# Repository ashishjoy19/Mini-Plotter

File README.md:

# Electronics 

# ⚡ Mini Plotter V2 – Electronics Documentation

## Overview

This document covers **the electronics subsystem** of the Mini Plotter V project.

It is intended as a **reference for coworkers, fabrication, debugging, and replication** of the electronics and PCB.

---

## Scope

### Included
- PCB design reference
- Power architecture
- Microcontroller pin mapping
- Stepper driver connections
- Peripheral interfaces

**Board Details**

| Parameter | Value |
|--------|------|
| PCB Name | Mini Plotter V2 – Electronics |
| Layers | 2 |
| Thickness | 1.6 mm |
| Copper Weight | 1 oz |
| Assembly | Through-hole + SMD |
| Logic Voltage | 3.3V |
| Motor Voltage | 5V DC |

## Power Architecture

### Power Input
- External DC input - USB C (Power only)
- Recommended supply: **5V**

### Voltage Rails
- **Motor Rail:** Direct from input to stepper drivers
- **Logic Rail:** Regulated 3.3V for MCU and peripherals

### Electrical Notes

⚠️ **Important**
- Power supply must handle motor current peaks
- Logic and motor grounds are common
- Do not connect or disconnect motors while powered

---

## MCU Pin Mapping

## GPIO Pin Mapping (Grouped)

### Motor 1 (Stepper)
| Label | GPIO |
|-----|------|
| IN1 | GPIO 23 |
| IN2 | GPIO 22 |
| IN3 | GPIO 21 |
| IN4 | GPIO 19 |

### Motor 2 (Stepper)
| Label | GPIO |
|-----|------|
| IN5 | GPIO 18 |
| IN6 | GPIO 17 |
| IN7 | GPIO 16 |
| IN8 | GPIO 4 |

### Servo Motor
| Label | GPIO |
|------|------|
| SIGNAL | GPIO 13 |
| VCC | 5V |
| GND | GND |

### Limit Switches
| Switch | Signal GPIO | Ground |
|-------|------------|--------|
| X Limit | GPIO 27 | GND |
| Y Limit | GPIO 14 | GND |

---

# ⚡ ESP32-WROOM-32E – PCB Design & Boot Guidelines

This document provides **electronics design guidelines** for using the **ESP32-WROOM-32E** module in custom PCBs.

It focuses on:
- Boot and flashing requirements
- Strapping pins and default states
- Pins to avoid or use with caution
- Minimum required external circuitry
- PCB layout considerations

---

## ESP32-WROOM-32E Overview

- MCU: ESP32 (dual-core Xtensa LX6)
- Operating Voltage: **3.3V**
- Wi-Fi + Bluetooth on-module
- Integrated antenna (keep-out required)

⚠️ **All GPIOs are 3.3V only. Do NOT apply 5V.**

---

## Minimum Circuit for Boot & Flash

::contentReference[oaicite:0]{index=0}

### Mandatory Connections

| Pin | Requirement |
|----|------------|
| 3V3 | Stable 3.3V supply (≥ 600 mA peak) |
| GND | Solid ground connection |
| EN | Pulled HIGH (via 10kΩ) |
| IO0 | Pulled HIGH (via 10kΩ) |
| TX0 (GPIO1) | UART TX for flashing |
| RX0 (GPIO3) | UART RX for flashing |

---

## Boot & Flash Logic

### Boot Mode Selection

| IO0 State | Boot Mode |
|---------|-----------|
| HIGH | Normal boot (flash) |
| LOW | UART download (flashing) |

To flash firmware:
- **IO0 = LOW**
- **EN toggled LOW → HIGH (reset)**

---

## Strapping Pins (CRITICAL)

These pins are sampled **at reset**.  
Incorrect levels will prevent booting.

| GPIO | Default State | Function |
|----|--------------|---------|
| GPIO0 | Pull-up | Boot mode select |
| GPIO2 | Pull-down | Must be LOW at boot |
| GPIO4 | Pull-down | Boot config |
| GPIO5 | Pull-up | Boot config |
| GPIO12 | Pull-down | Flash voltage select |
| GPIO15 | Pull-up | Boot config |

⚠️ **Do not drive these pins externally at boot unless you know the impact.**

---

## Pin Usage Guidelines

### Pins to Avoid (or Use Carefully)

| GPIO | Reason |
|----|-------|
| GPIO6–11 | Connected to internal flash (DO NOT USE) |
| GPIO0 | Boot mode pin |
| GPIO2 | Must be LOW during boot |
| GPIO12 | Affects flash voltage |
| GPIO15 | Boot strapping pin |

---

### Recommended Safe GPIOs

| GPIO | Notes |
|----|------|
| GPIO4 | Safe after boot |
| GPIO5 | Safe after boot |
| GPIO16–19 | General purpose |
| GPIO21–23 | I²C / SPI friendly |
| GPIO25–27 | ADC capable |
| GPIO32–33 | ADC + low power |
| GPIO34–39 | Input-only (ADC) |

---

## Pull-Up / Pull-Down Requirements

### Required External Resistors

| Pin | Recommended |
|----|-------------|
| EN | 10kΩ pull-up to 3.3V |
| IO0 | 10kΩ pull-up |
| GPIO2 | 10kΩ pull-down |
| GPIO12 | 10kΩ pull-down |
| GPIO15 | 10kΩ pull-up |

⚠️ Internal pulls exist but **external resistors improve reliability**.

---

## Reset & Auto-Flash Circuit (Recommended)

For USB-UART auto programming:

| ESP32 Pin | USB-UART Signal |
|--------|----------------|
| EN | DTR (via transistor) |
| IO0 | RTS (via transistor) |
| RX0 | TXD |
| TX0 | RXD |

This allows flashing via:
- Arduino IDE
- ESP-IDF
- PlatformIO

---

## Power Supply Design Notes

- Use **LDO or buck regulator** capable of **600–800 mA**
- Place **10µF + 0.1µF decoupling capacitors** close to 3V3 pin
- Keep power traces wide and short

⚠️ Brownouts are the #1 cause of ESP32 instability.

---

## Antenna & RF Layout Rules

⚠️ **Very Important**

- Keep copper **clear under antenna**
- No ground pours or traces under antenna area
- Follow Espressif keep-out recommendations
- Place module at PCB edge if possible

---

## Common Design Mistakes

❌ Powering ESP32 from 5V  
❌ Using GPIO6–11  
❌ Driving strapping pins at boot  
❌ Weak 3.3V regulator  
❌ Traces under antenna  

---

## Recommended Bring-Up Checklist

1. Verify 3.3V rail (no load)
2. Check EN pulled HIGH
3. Check IO0 pulled HIGH
4. Reset → observe serial output
5. Pull IO0 LOW → reset → flash test firmware

---

## Reference

- ESP32-WROOM-32E Datasheet
- Espressif Hardware Design Guidelines

---

## Notes

This document is intended for **PCB designers and electronics engineers** working with ESP32-WROOM-32E in custom hardware.

Keep this file updated if pin usage or constraints change.

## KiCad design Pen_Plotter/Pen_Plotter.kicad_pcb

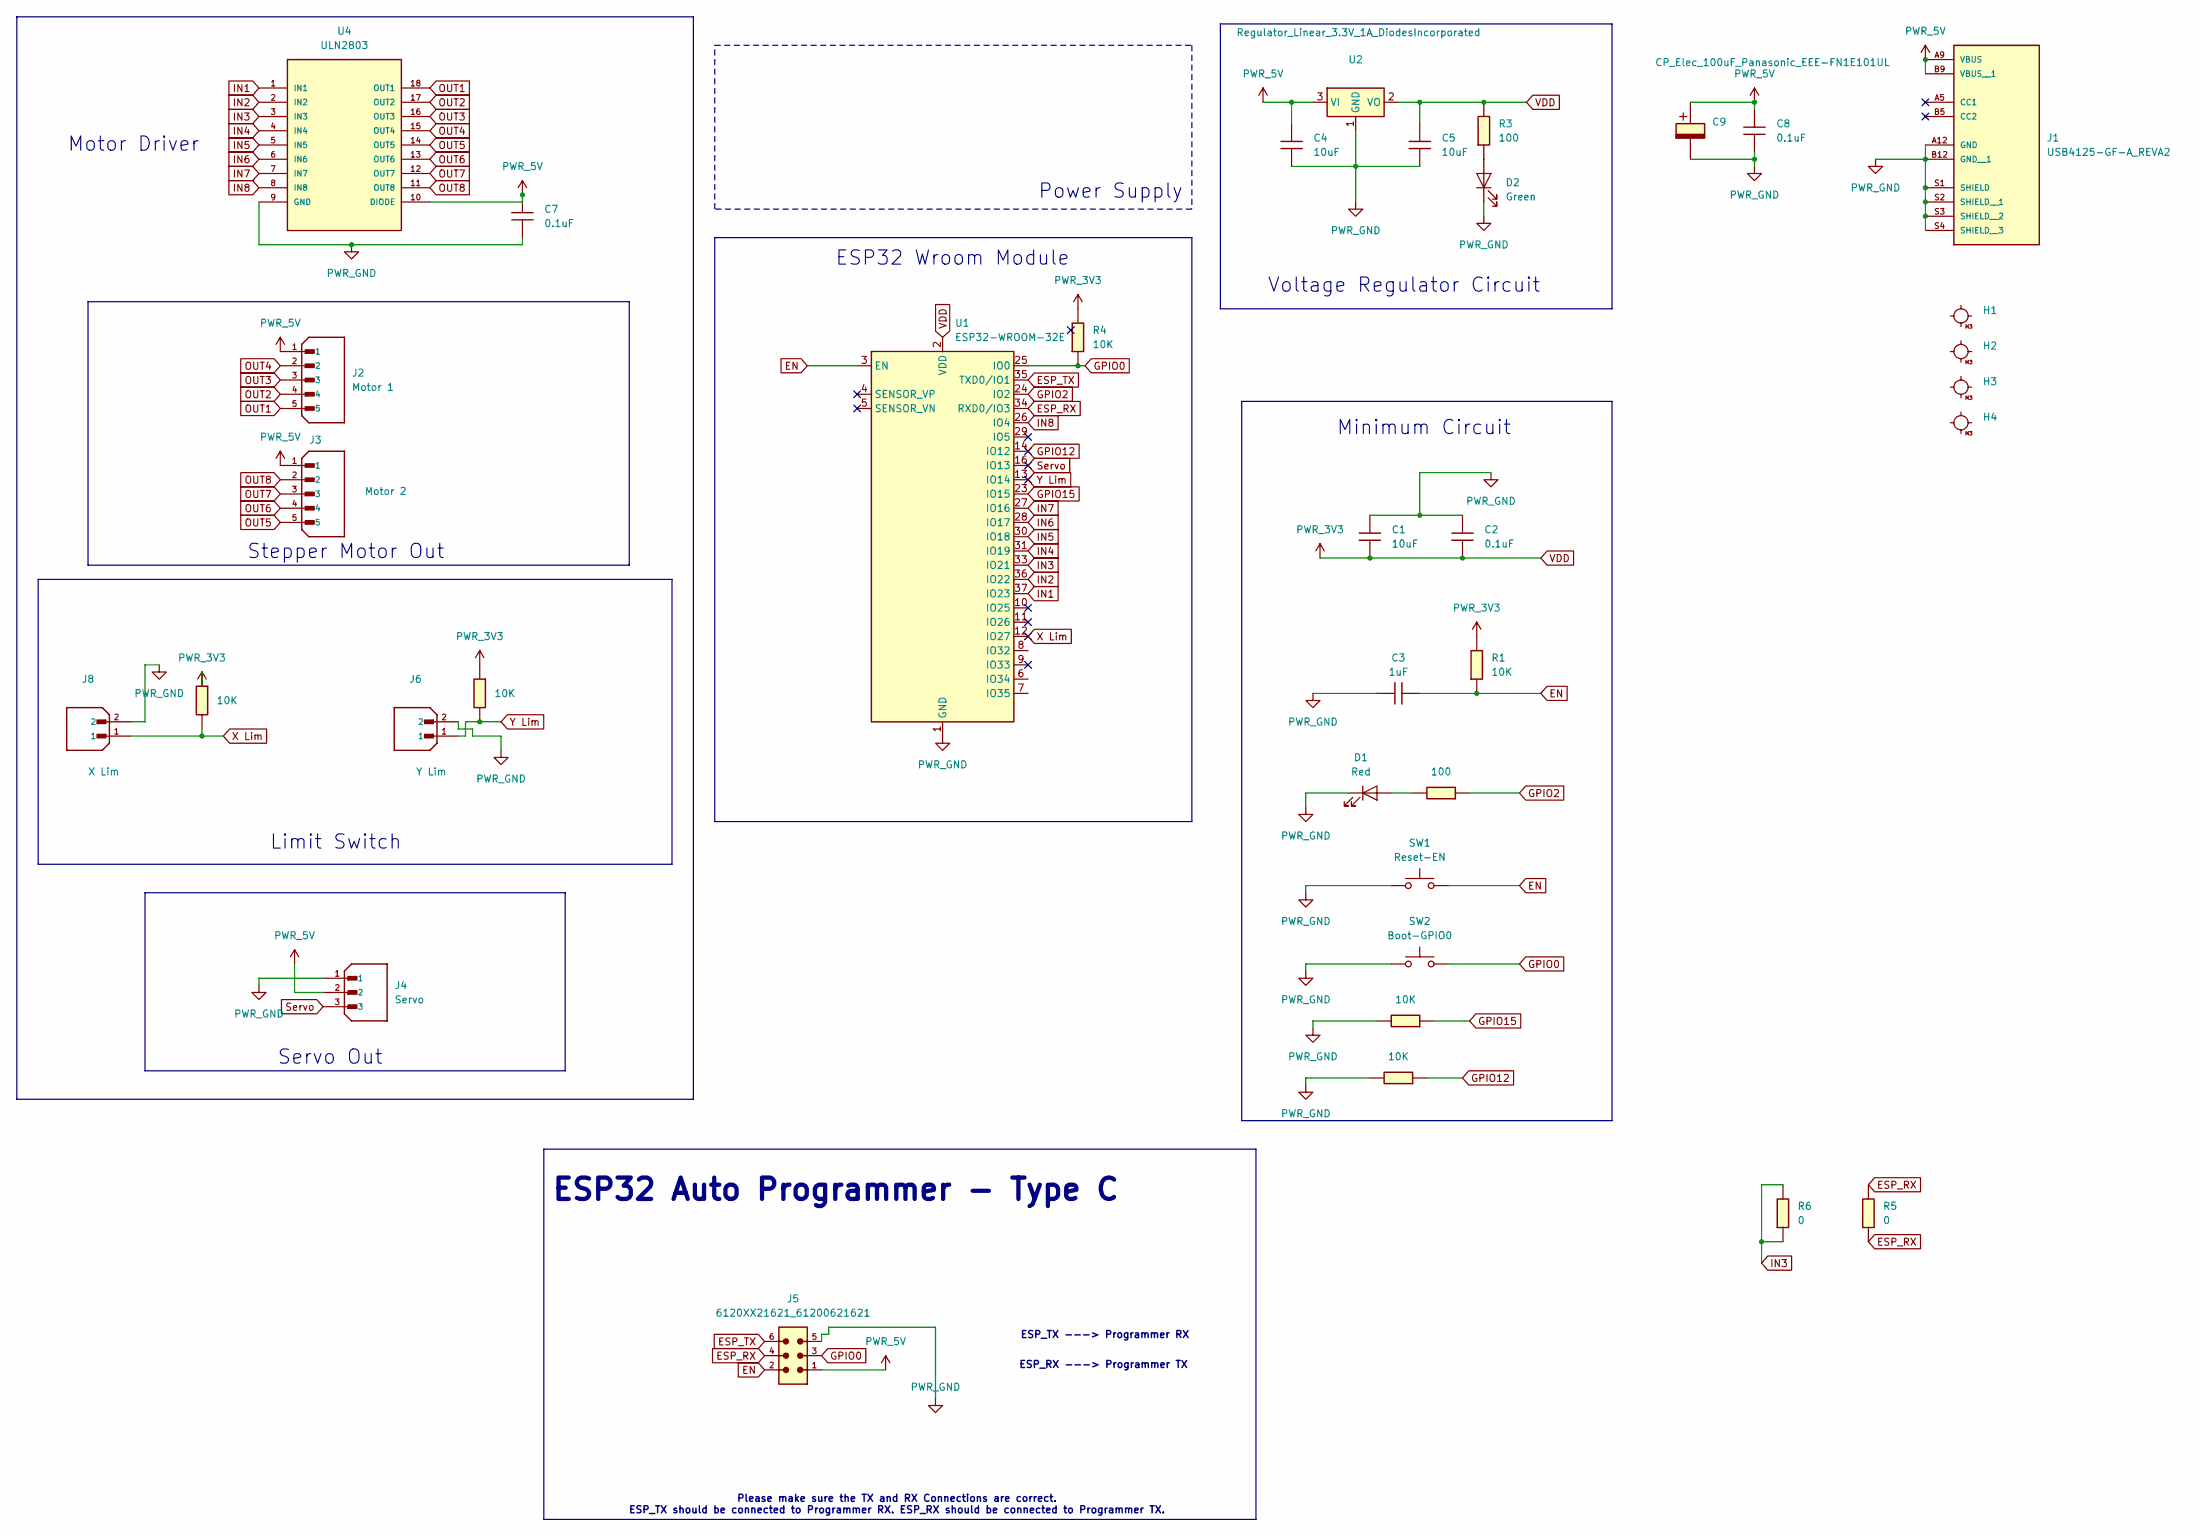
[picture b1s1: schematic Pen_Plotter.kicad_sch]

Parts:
C1, C4, C5: 10uF; C_1206
C2, C7, C8: 0.1uF; C_1206
C3: 1uF; C_1206
C9: CP_Elec_100uF_Panasonic_EEE-FN1E101UL
D1: Red; LED_1206
D2: Green; LED_1206
H1, H2, H3, H4: MountingHole_M3
J1: USB4125-GF-A_REVA2; GCT_USB4125-GF-A_REVA2; PARTREV Rev A2
J2: Motor 1; JST_B5B-XH-A; PARTREV 7/4/21
J3: Motor 2; JST_B5B-XH-A; PARTREV 7/4/21
J4: Servo; JST_B3B-XH-A; PARTREV 7/4/21
J5: 6120XX21621_61200621621; 61200621621
J6: Y Lim; JST_B2B-XH-A_LF__SN_; PARTREV N/A
J8: X Lim; JST_B2B-XH-A_LF__SN_; PARTREV N/A
R1, R4, R8, R9, R10, R11: 10K; R_1206
R2, R3: 100; R_1206
R5, R6: 0; R_1206
SW1: Reset-EN; Button_Omron_B3SN_6.0x6.0mm
SW2: Boot-GPIO0; Button_Omron_B3SN_6.0x6.0mm
U1: ESP32-WROOM-32E; ESP32-WROOM-32D
U2: Regulator_Linear_3.3V_1A_DiodesIncorporated; SOT-223-3_TabPin2
U4: ULN2803; SO18L

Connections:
EN: C3.1, J5.2, R1.2, SW1.2, U1.3 (EN)
ESP_RX: J5.4, R5.1, R5.2, U1.34 (RXD0/IO3)
ESP_TX: J5.6, U1.35 (TXD0/IO1)
GPIO0: J5.3, R4.2, SW2.2, U1.25 (IO0)
GPIO2: R2.2, U1.24 (IO2)
GPIO12: R11.2, U1.14 (IO12)
GPIO15: R8.2, U1.23 (IO15)
IN1: U1.37 (IO23), U4.1 (IN1)
IN2: U1.36 (IO22), U4.2 (IN2)
IN3: R6.1, R6.2, U1.33 (IO21), U4.3 (IN3)
IN4: U1.31 (IO19), U4.4 (IN4)
IN5: U1.30 (IO18), U4.5 (IN5)
IN6: U1.28 (IO17), U4.6 (IN6)
IN7: U1.27 (IO16), U4.7 (IN7)
IN8: U1.26 (IO4), U4.8 (IN8)
unnamed: D1.2 (A), R2.1
unnamed: D2.2 (A), R3.2
OUT1: J2.5, U4.18 (OUT1)
OUT2: J2.4, U4.17 (OUT2)
OUT3: J2.3, U4.16 (OUT3)
OUT4: J2.2, U4.15 (OUT4)
OUT5: J3.5, U4.14 (OUT5)
OUT6: J3.4, U4.13 (OUT6)
OUT7: J3.3, U4.12 (OUT7)
OUT8: J3.2, U4.11 (OUT8)
PWR_5V: C4.1, C7.1, C8.1, C9.1, J1.A9 (VBUS), J1.B9 (VBUS__1), J2.1, J3.1, J4.2, J5.1, U2.3 (VI), U4.10 (DIODE)
PWR_GND: C1.1, C2.1, C3.2, C4.2, C5.2, C7.2, C8.2, C9.2, D1.1 (K), D2.1 (K), J1.A12 (GND), J1.B12 (GND__1), J1.S1 (SHIELD), J1.S2 (SHIELD__1), J1.S3 (SHIELD__2), J1.S4 (SHIELD__3), J4.1, J5.5, J6.2, J8.2, R8.1, R11.1, SW1.1, SW2.1, U1.1 (GND), U1.15 (GND), U1.38 (GND), U1.39 (GND), U2.1 (GND), U4.9 (GND)
Servo: J4.3, U1.16 (IO13)
VDD: C1.2, C2.2, C5.1, R1.1, R3.1, R4.1, R9.2, R10.2, U1.2 (VDD), U2.2 (VO)
X Lim: J8.1, R10.1, U1.12 (IO27)
Y Lim: J6.1, R9.1, U1.13 (IO14)

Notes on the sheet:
ESP_TX ---> Programmer RX
Limit Switch
ESP_RX ---> Programmer TX
Minimum Circuit
ESP32 Auto Programmer - Type C
Stepper Motor Out
Power Supply
Please make sure the TX and RX Connections are correct. ESP_TX should be connected to Programmer RX. ESP_RX should be connected to Programmer TX.
Servo Out
Motor Driver
Voltage Regulator Circuit
ESP32 Wroom Module

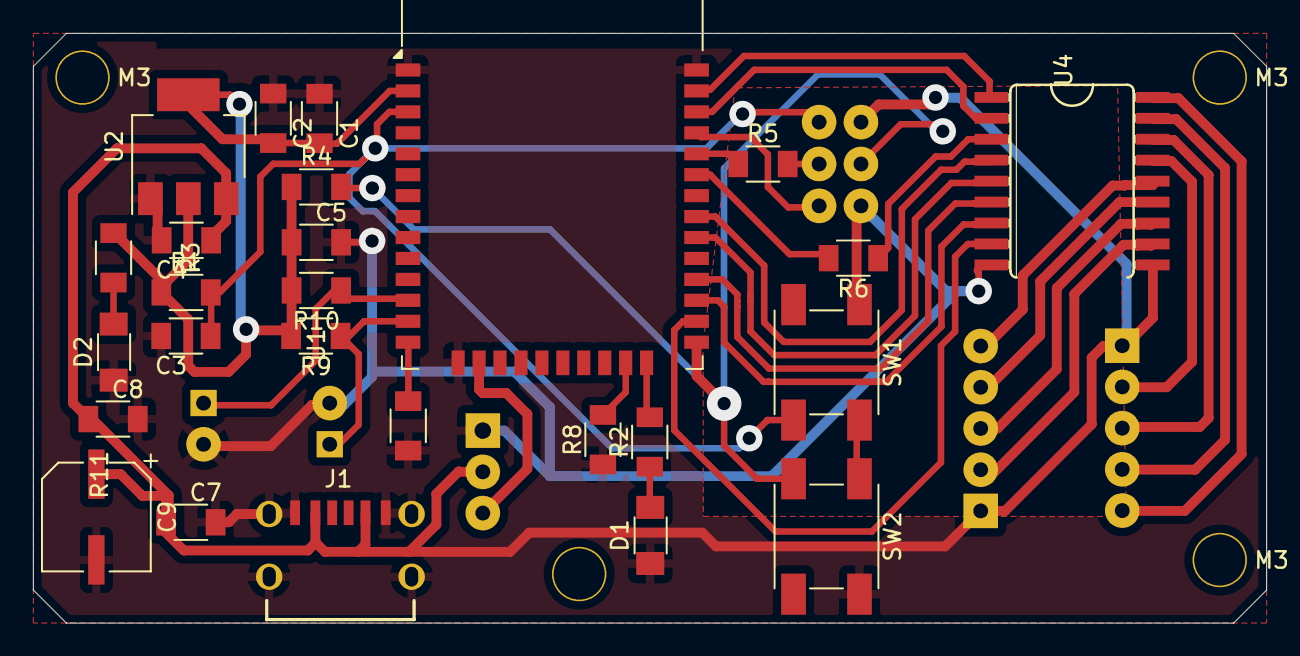
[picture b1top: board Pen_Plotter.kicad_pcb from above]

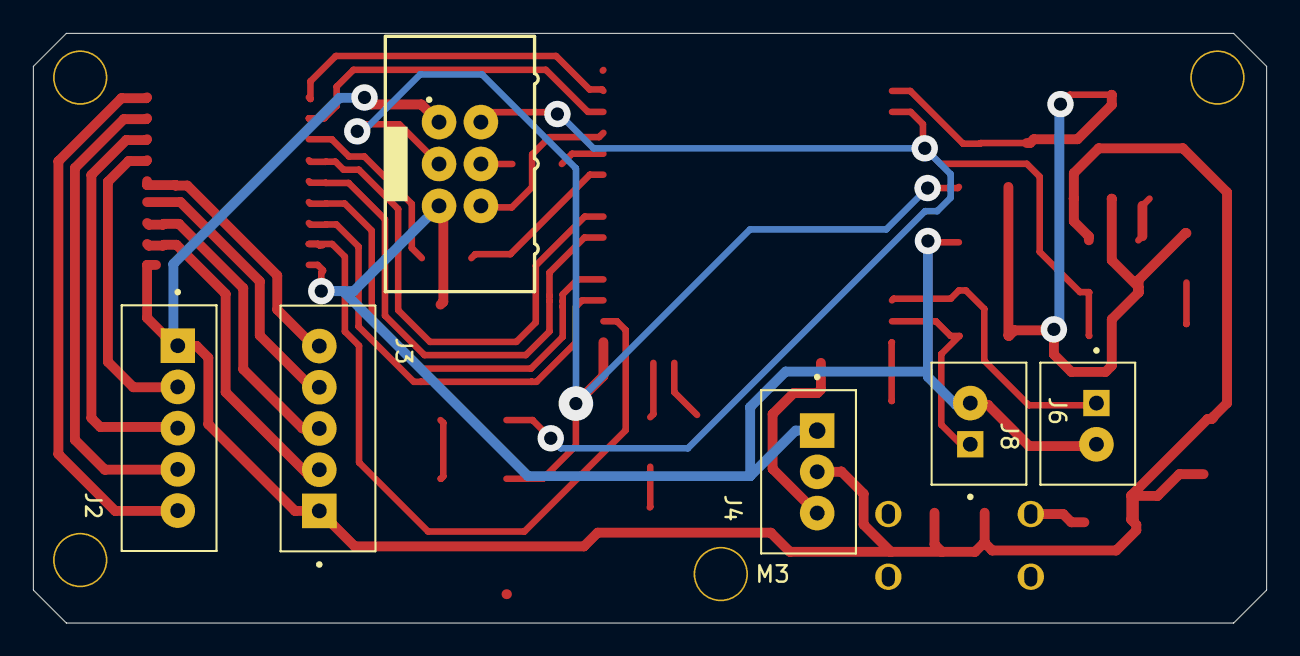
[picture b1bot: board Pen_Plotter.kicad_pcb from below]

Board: 2 copper layers, 74.8 x 35.8 mm, 36 parts (7 on the bottom side), 31 nets.

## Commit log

2026-01-05 schematic v1
2026-01-05 Added some text
2026-01-06 6 January
2026-01-06 Wired THT Components
2026-01-06 Version with Auto Programmer, USBC and CH340 IC
2026-01-06 Schematic Excluded USBC, CH340IC, Autoprogrammer PCB: Removed components
2026-01-13 PCB for ESP UCap
2026-01-13 Mini Plotter PCB 13
2026-01-13 added gerber files
2026-01-17 First PCB Final - Problems with RX-TX
2026-01-17 PCB _ TX and RX Corrected
2026-01-17 Gitlab and Github push test
2026-01-17 second push test
2026-01-17 PCB V2.1
2026-01-19 Inverted IDC Connector position and thickened traces
2026-01-19 CAD Components added
2026-01-19 FInal PCB V@, ready for milling
2026-01-19 PCB V2 Draft
2026-01-20 Final PCB Milling done; Retraced traces to top
2026-01-23 updated readme file
